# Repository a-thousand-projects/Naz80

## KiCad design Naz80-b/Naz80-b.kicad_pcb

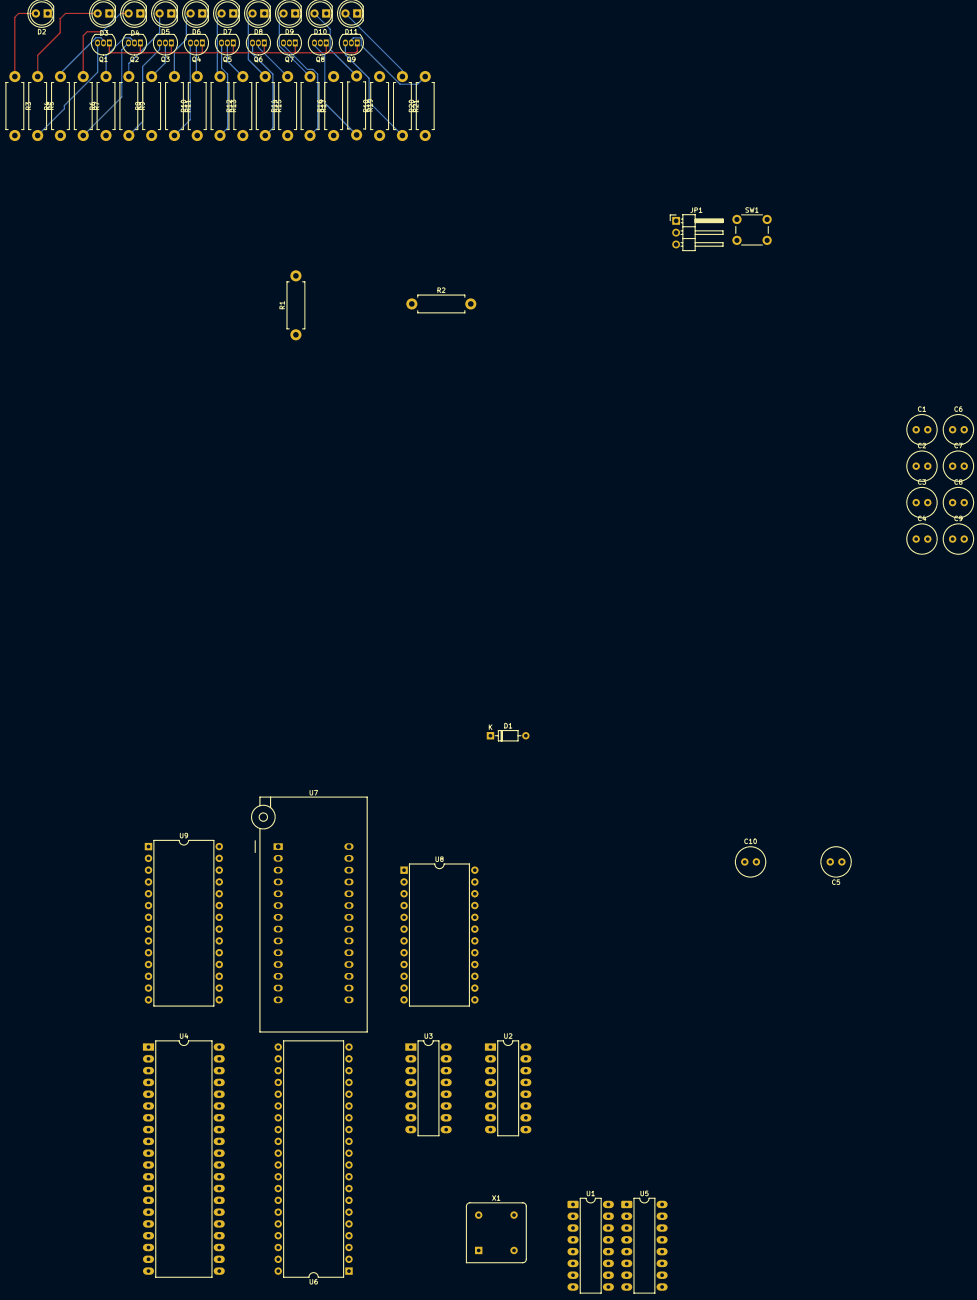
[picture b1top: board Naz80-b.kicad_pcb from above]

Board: 2 copper layers, 63 parts (0 on the bottom side), 71 nets.

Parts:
C1: 1uF; C_Radial_D6.3mm_H7.0mm_P2.50mm
C2, C3, C4, C5, C6, C7, C8, C9, C10: 0.1uF; C_Radial_D6.3mm_H7.0mm_P2.50mm
D1: 1N4148; D_DO-35_SOD27_P7.62mm_Horizontal
D2, D3, D4, D5, D6, D7, D8, D9, D10, D11: LED; LED_D5.0mm
JP1: ROM BANK Selector; PinHeader_1x03_P2.54mm_Horizontal
Q1, Q2, Q3, Q4, Q5, Q6, Q7, Q8, Q9: 2N3906; TO-92_Inline
R1: 2k; R_Axial_DIN0411_L9.9mm_D3.6mm_P12.70mm_Horizontal
R2, R4, R6, R8, R10, R12, R14, R16, R18, R20: 1k; R_Axial_DIN0411_L9.9mm_D3.6mm_P12.70mm_Horizontal
R3, R5, R7, R9, R11, R13, R15, R17, R19, R21: 330; R_Axial_DIN0411_L9.9mm_D3.6mm_P12.70mm_Horizontal
SW1: SW_Push; SW_PUSH_6mm_H9.5mm
U1: 74LS14; DIP-16_W7.62mm_LongPads
U2: 74LS04; DIP-16_W7.62mm_LongPads
U3: 74LS32; DIP-16_W7.62mm_LongPads
U4: Z80CPU; DIP-40_W15.24mm_LongPads
U5: 74LS139; DIP-16_W7.62mm_LongPads
U6: 82C55A; DIP-40_W15.24mm
U7: W27C512; DIP_Socket-28_W11.9_W12.7_W15.24_W17.78_W18.5_3M_228-1277-0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
U8: MC68B50; DIP-24_W15.24mm
U9: HM62256BLP; DIP-28_W15.24mm
X1: CXO_DIP8; Oscillator_DIP-8

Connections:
+5V: C2.1, C3.1, C4.1, C5.1, C6.1, C7.1, C8.1, C9.1, C10.1, D1.1 (K), JP1.3 (B), Q1.1 (E), Q2.1 (E), Q3.1 (E), Q4.1 (E), Q5.1 (E), Q6.1 (E), Q7.1 (E), Q8.1 (E), Q9.1 (E), R2.1, R3.2, U1.14 (VCC), U2.14 (VCC), U3.14 (VCC), U4.11 (VCC), U4.24 (~WAIT), U4.25 (~BUSRQ), U5.16 (VCC), U7.28 (VCC), U8.12 (VCC), U9.28 (VCC), X1.8 (Vcc)
/A0: U4.30 (A0), U7.10 (A0), U8.11 (RS), U9.10 (A0)
/A1: U4.31 (A1), U7.9 (A1), U9.9 (A1)
/A2: U4.32 (A2), U7.8 (A2), U9.8 (A2)
/A3: U4.33 (A3), U7.7 (A3), U9.7 (A3)
/A4: U4.34 (A4), U7.6 (A4), U9.6 (A4)
/A5: U4.35 (A5), U7.5 (A5), U9.5 (A5)
/A6: U4.36 (A6), U7.4 (A6), U9.4 (A6)
/A7: U4.37 (A7), U7.3 (A7), U9.3 (A7)
/A8: U4.38 (A8), U7.25 (A8), U9.25 (A8)
/A9: U4.39 (A9), U7.24 (A9), U9.24 (A9)
/A10: U4.40 (A10), U7.21 (A10), U9.21 (A10)
/A11: U4.1 (A11), U7.23 (A11), U9.23 (A11)
/A12: U4.2 (A12), U7.2 (A12), U9.2 (A12)
/A13: U4.3 (A13), U7.26 (A13), U9.26 (A13)
/A14: U4.4 (A14), U7.27 (A14), U9.1 (A14)
/A15: U2.1, U4.5 (A15), U7.20 (*CE)
/D0: U4.14 (D0), U7.11 (Q0), U8.22 (D0), U9.11 (Q0)
/D1: U4.15 (D1), U7.12 (Q1), U8.21 (D1), U9.12 (Q1)
/D2: U4.12 (D2), U7.13 (Q2), U8.20 (D2), U9.13 (Q2)
/D3: U4.8 (D3), U7.15 (Q3), U8.19 (D3), U9.15 (Q3)
/D4: U4.7 (D4), U7.16 (Q4), U8.18 (D4), U9.16 (Q4)
/D5: U4.9 (D5), U7.17 (Q5), U8.17 (D5), U9.17 (Q5)
/D6: U4.10 (D6), U7.18 (Q6), U8.16 (D6), U9.18 (Q6)
/D7: U4.13 (D7), U7.19 (Q7), U8.15 (D7), U9.19 (Q7)
/Indicators/~MREQ: R16.1, R20.1
/RESET: U1.2, U1.3
/~IO_WE: U3.11, U8.13 (R/~W)
/~MREQ: U3.2, U3.4, U4.19 (~MREQ)
/~M_OE: U3.3, U7.22 (*OE/VPP), U9.22 (~OE)
/~RD: U3.1, U3.9, U4.21 (~RD)
/~RESET: U1.4, U4.26 (~RESET)
/~WR: U3.5, U3.13, U4.22 (~WR)
CLK: U4.6 (~CLK), U8.3 (Rx_CLK), U8.4 (Tx_CLK), X1.5 (OUT)
GND: C1.2, C2.2, C3.2, C4.2, C5.2, C6.2, C7.2, C8.2, C9.2, C10.2, D2.1 (K), D3.1 (K), D4.1 (K), D5.1 (K), D6.1 (K), D7.1 (K), D8.1 (K), D9.1 (K), D10.1 (K), D11.1 (K), JP1.1 (A), SW1.1, U1.7 (GND), U2.7 (GND), U3.7 (GND), U4.29 (GND), U5.8 (GND), U7.14 (GND), U8.1 (VSS), U8.9 (CS2), U9.14 (GND), X1.4 (GND)
unnamed: C1.1, D1.2 (A), R1.2, R2.2, U1.1
unnamed: D2.2 (A), R3.1
unnamed: D3.2 (A), R5.1
unnamed: D4.2 (A), R7.1
unnamed: D5.2 (A), R9.1
unnamed: D6.2 (A), R11.1
unnamed: D7.2 (A), R13.1
unnamed: D8.2 (A), R15.1
unnamed: D9.2 (A), R17.1
unnamed: D10.2 (A), R19.1
unnamed: D11.2 (A), R21.1
unnamed: Q1.2 (B), R4.2
unnamed: Q1.3 (C), R5.2
unnamed: Q2.2 (B), R6.2
unnamed: Q2.3 (C), R7.2
unnamed: Q3.2 (B), R8.2
unnamed: Q3.3 (C), R9.2
unnamed: Q4.2 (B), R10.2
unnamed: Q4.3 (C), R11.2
unnamed: Q5.2 (B), R12.2
unnamed: Q5.3 (C), R13.2
unnamed: Q6.2 (B), R14.2
unnamed: Q6.3 (C), R15.2
unnamed: Q7.2 (B), R16.2
unnamed: Q7.3 (C), R17.2
unnamed: Q8.2 (B), R18.2
unnamed: Q8.3 (C), R19.2
unnamed: Q9.2 (B), R20.2
unnamed: Q9.3 (C), R21.2
unnamed: R1.1, SW1.2
unnamed: U2.4, U8.14 (E)
unnamed: U2.2, U9.20 (~CS)
RB: JP1.2 (C), U7.1 (A15)
~INT: U4.16 (~INT), U8.7 (~IRQ)
~IORQ: U2.3, U3.10, U3.12, U4.20 (~IORQ)
~M1: U4.27 (~M1), U8.8 (CS0)
